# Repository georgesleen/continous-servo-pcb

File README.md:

# Continous rotation servo PCB.

Based on the final project from ENPH259. I've extended the project by creating a PCB and mechanical mount for the project.

I've also included an optional 'speed readout' on the board itself. This displays the current revolutions per cycle of the servo in binary.

By using slots in a disk attached to the motor shaft, I can monitor the rotational speed of the motor. This can then be fed into a counter that resets periodically, and is latched right before every reset. This digital number is then put through an R2R DAC, which is then compared with a reference voltage and fed into a PI controller, that runs a MOSFET driving the motor.

The project requires an external 5V, GND, -5V, and 5 Hz clock signal.

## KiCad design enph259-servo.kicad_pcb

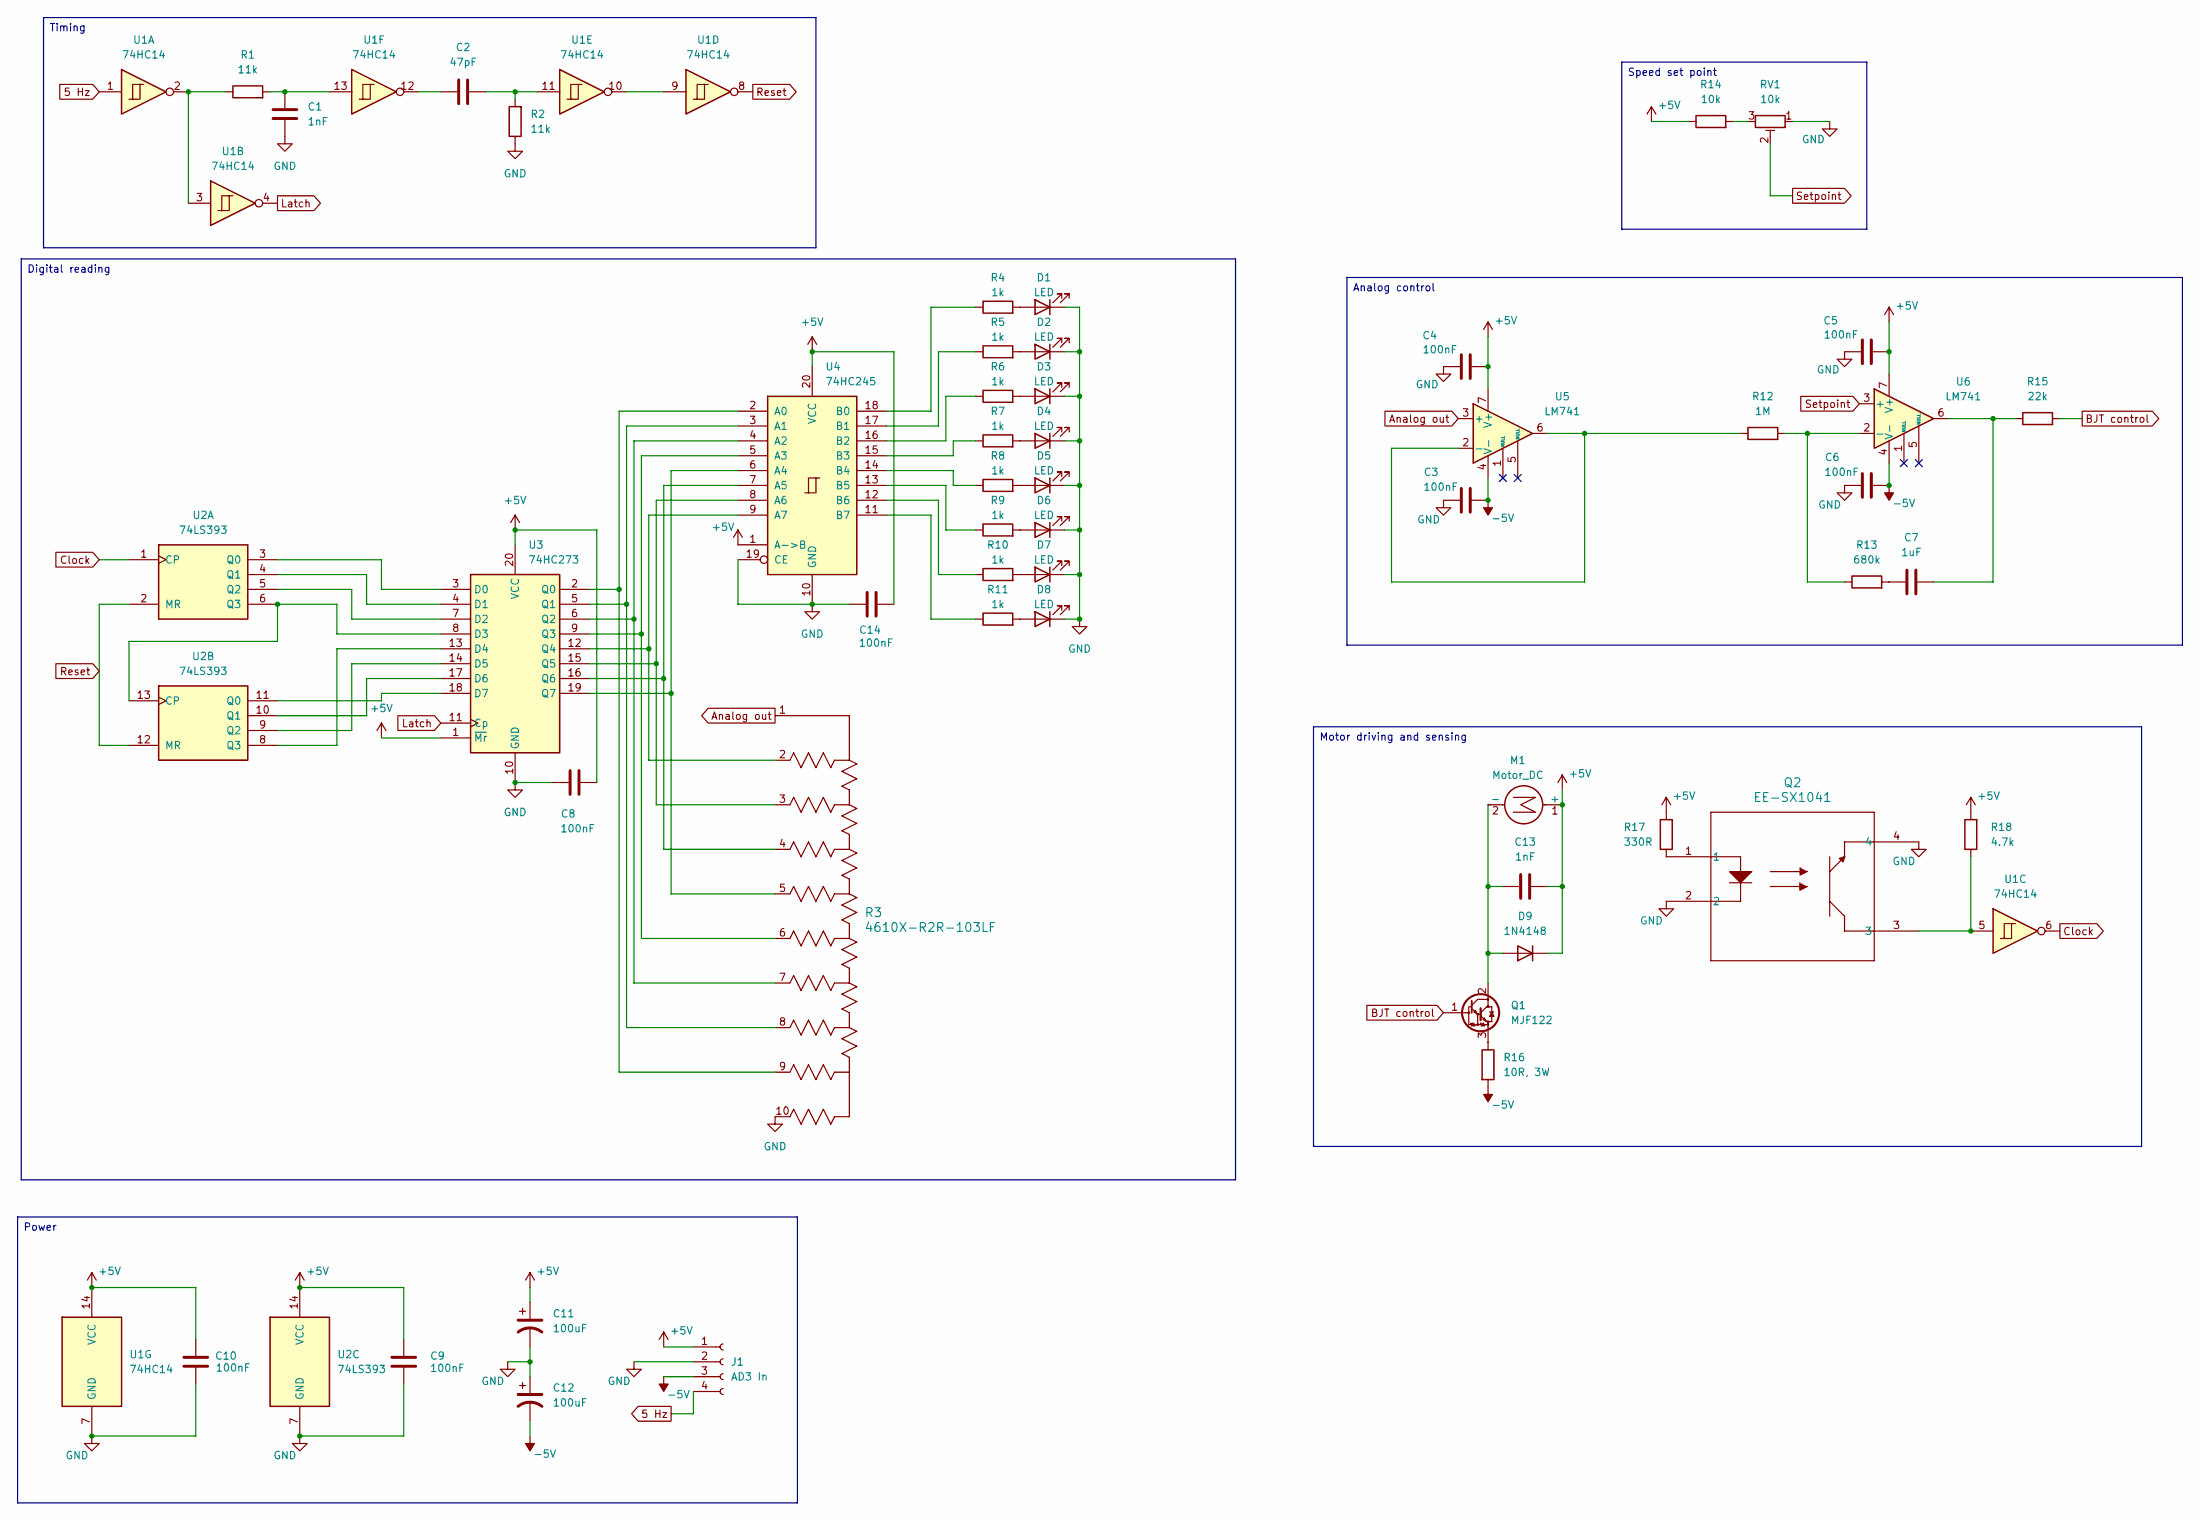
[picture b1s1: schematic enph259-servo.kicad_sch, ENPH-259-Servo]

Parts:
C1, C13: 1nF; C_Rect_L7.0mm_W2.5mm_P5.00mm
C2: 47pF; C_Disc_D3.0mm_W1.6mm_P2.50mm
C3, C4, C5, C6, C8, C9, C10, C14: 100nF; C_Rect_L7.0mm_W2.5mm_P5.00mm
C7: 1uF; C_Rect_L10.3mm_W5.0mm_P7.50mm_MKS4
C11, C12: 100uF; CP_Radial_D6.3mm_P2.50mm
D1, D2, D3, D4, D5, D6, D7, D8: LED; LED_D5.0mm
D9: 1N4148; D_DO-35_SOD27_P7.62mm_Horizontal
J1: AD3 In; PinHeader_1x04_P2.54mm_Vertical
M1: Motor_DC; PinSocket_1x02_P2.54mm_Vertical
Q1: MJF122; TO-220-3_Vertical
Q2: EE-SX1041; PinSocket_1x04_P2.54mm_Vertical
R1, R2: 11k; R_Axial_DIN0309_L9.0mm_D3.2mm_P12.70mm_Horizontal
R3: 4610X-R2R-103LF; R_Array_SIP10
R4, R5, R6, R7, R8, R9, R10, R11: 1k; R_Axial_DIN0309_L9.0mm_D3.2mm_P12.70mm_Horizontal
R12: 1M; R_Axial_DIN0309_L9.0mm_D3.2mm_P12.70mm_Horizontal
R13: 680k; R_Axial_DIN0309_L9.0mm_D3.2mm_P12.70mm_Horizontal
R14: 10k; R_Axial_DIN0309_L9.0mm_D3.2mm_P12.70mm_Horizontal
R15: 22k; R_Axial_DIN0309_L9.0mm_D3.2mm_P12.70mm_Horizontal
R16: 10R, 3W; R_Axial_DIN0414_L11.9mm_D4.5mm_P15.24mm_Horizontal
R17: 330R; R_Axial_DIN0309_L9.0mm_D3.2mm_P12.70mm_Horizontal
R18: 4.7k; R_Axial_DIN0309_L9.0mm_D3.2mm_P12.70mm_Horizontal
RV1: 10k; Potentiometer_Bourns_3296W_Vertical
U1: 74HC14; DIP-14_W7.62mm_Socket
U2: 74LS393; DIP-14_W7.62mm_Socket
U3: 74HC273; DIP-20_W7.62mm_Socket
U4: 74HC245; DIP-20_W7.62mm_Socket
U5, U6: LM741; DIP-8_W7.62mm_Socket

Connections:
5 Hz: J1.4, U1.1
+5V: C4.1, C5.1, C8.1, C9.1, C10.1, C11.1, C13.2, C14.2, D9.1 (K), J1.1, M1.1 (+), R14.1, R17.2, R18.2, U1.14 (VCC), U2.14 (VCC), U3.1 (~Mr), U3.20 (VCC), U4.1 (A->B), U4.20 (VCC), U5.7 (V+), U6.7 (V+)
-5V: C3.1, C6.1, C12.2, J1.3, R16.2, U5.4 (V-), U6.4 (V-)
Analog out: R3.1, U5.3 (+)
BJT control: Q1.1 (B), R15.2
Clock: U1.6, U2.1 (CP)
GND: C1.2, C3.2, C4.2, C5.2, C6.2, C8.2, C9.2, C10.2, C11.2, C12.1, C14.1, D1.1 (K), D2.1 (K), D3.1 (K), D4.1 (K), D5.1 (K), D6.1 (K), D7.1 (K), D8.1 (K), J1.2, Q2.2, Q2.4, R2.1, R3.10, RV1.1, U1.7 (GND), U2.7 (GND), U3.10 (GND), U4.10 (GND), U4.19 (CE)
Latch: U1.4, U3.11 (Cp)
unnamed: C1.1, R1.2, U1.13
unnamed: C2.1, U1.12
unnamed: C2.2, R2.2, U1.11
unnamed: C7.1, R13.2
unnamed: C7.2, R15.1, U6.6
unnamed: D1.2 (A), R4.2
unnamed: D2.2 (A), R5.2
unnamed: D3.2 (A), R6.2
unnamed: D4.2 (A), R7.2
unnamed: D5.2 (A), R8.2
unnamed: D6.2 (A), R9.2
unnamed: D7.2 (A), R10.2
unnamed: D8.2 (A), R11.2
unnamed: C13.1, D9.2 (A), M1.2 (-), Q1.2 (C)
unnamed: Q1.3 (E), R16.1
unnamed: Q2.1, R17.1
unnamed: Q2.3, R18.1, U1.5
unnamed: R1.1, U1.2, U1.3
unnamed: R14.2, RV1.3
unnamed: U1.9, U1.10
unnamed: U2.3 (Q0), U3.3 (D0)
unnamed: U2.4 (Q1), U3.4 (D1)
unnamed: U2.5 (Q2), U3.7 (D2)
unnamed: U2.6 (Q3), U2.13 (CP), U3.8 (D3)
unnamed: U2.11 (Q0), U3.18 (D7)
unnamed: U2.10 (Q1), U3.17 (D6)
unnamed: U2.9 (Q2), U3.14 (D5)
unnamed: U2.8 (Q3), U3.13 (D4)
unnamed: R3.9, U3.2 (Q0), U4.2 (A0)
unnamed: R3.8, U3.5 (Q1), U4.3 (A1)
unnamed: R3.7, U3.6 (Q2), U4.4 (A2)
unnamed: R3.6, U3.9 (Q3), U4.5 (A3)
unnamed: R3.2, U3.12 (Q4), U4.9 (A7)
unnamed: R3.3, U3.15 (Q5), U4.8 (A6)
unnamed: R3.4, U3.16 (Q6), U4.7 (A5)
unnamed: R3.5, U3.19 (Q7), U4.6 (A4)
unnamed: R4.1, U4.18 (B0)
unnamed: R5.1, U4.17 (B1)
unnamed: R6.1, U4.16 (B2)
unnamed: R7.1, U4.15 (B3)
unnamed: R8.1, U4.14 (B4)
unnamed: R9.1, U4.13 (B5)
unnamed: R10.1, U4.12 (B6)
unnamed: R11.1, U4.11 (B7)
unnamed: R12.1, U5.2 (-), U5.6
unnamed: R12.2, R13.1, U6.2 (-)
Reset: U1.8, U2.2 (MR), U2.12 (MR)
Setpoint: RV1.2, U6.3 (+)

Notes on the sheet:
Digital reading
Motor driving and sensing
Power
Speed set point
Analog control
Timing

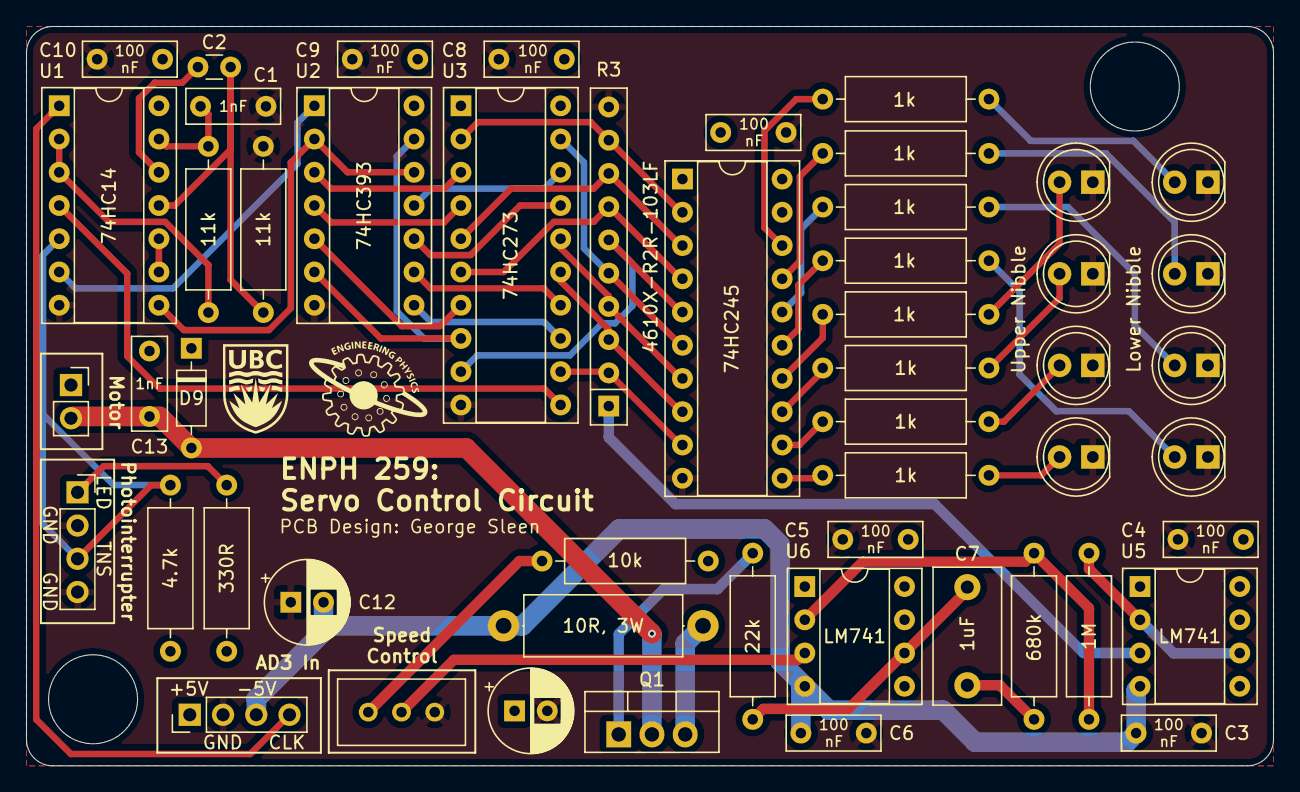
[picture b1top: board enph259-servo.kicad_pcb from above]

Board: 4 copper layers, 95.3 x 56.5 mm, 52 parts (0 on the bottom side), 56 nets.

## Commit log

2025-03-09 Import existing project
2025-06-10 Add some mount mechanical cad
2025-06-10 standardize capitalization
2025-06-10 Do not ignore production outputs
2025-06-10 Refactor project structure
2025-06-10 Add GNU 3.0 licence to the project
